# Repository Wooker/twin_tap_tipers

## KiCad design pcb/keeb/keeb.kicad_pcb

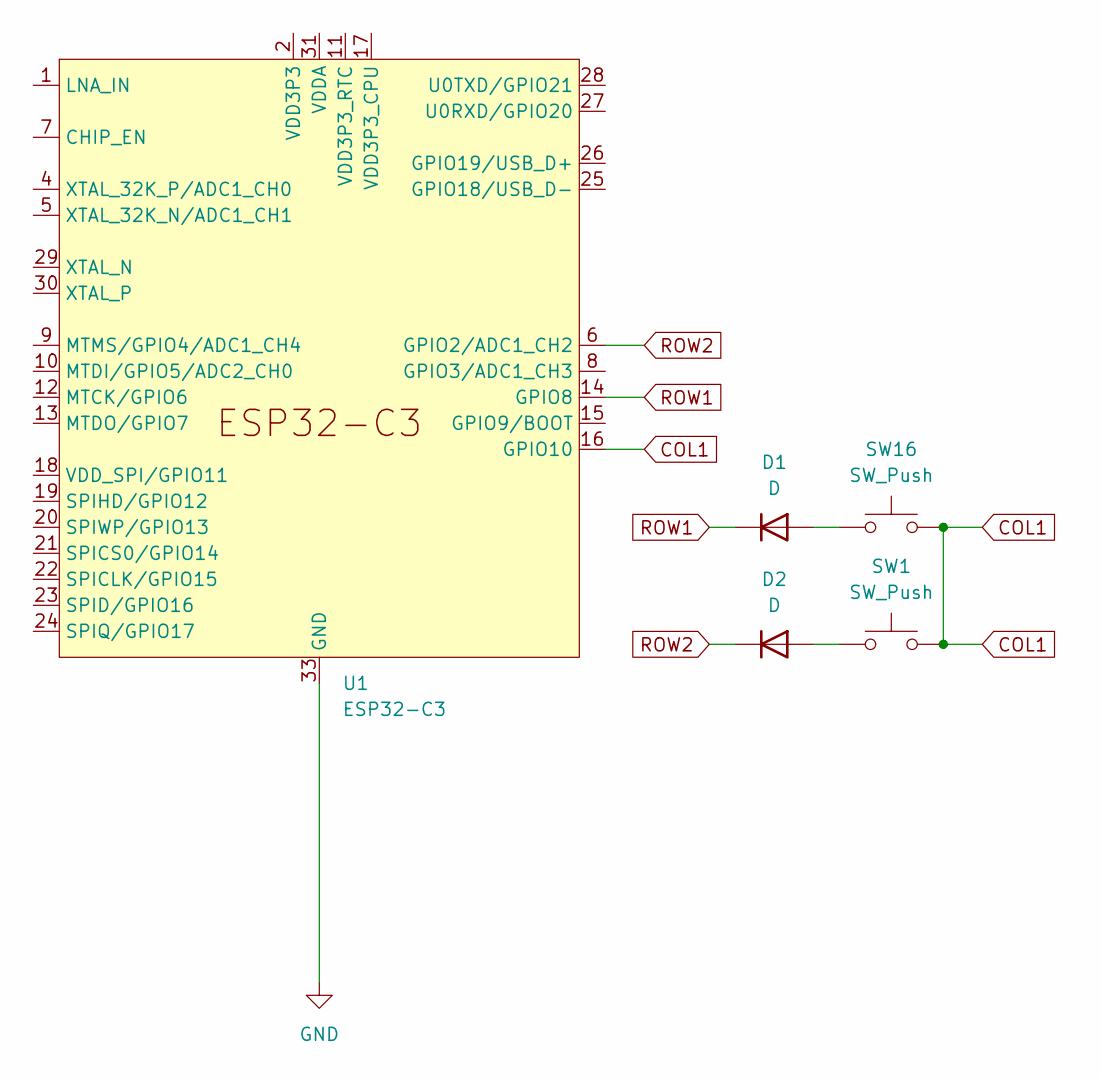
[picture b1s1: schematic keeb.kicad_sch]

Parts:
D1, D2: D; D_SOD-323_HandSoldering
SW1, SW16: SW_Push; SKPMAPE010
U1: ESP32-C3; QFN-32-1EP_5x5mm_P0.5mm_EP3.45x3.45mm

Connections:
COL1: SW1.2, SW16.2, U1.16 (GPIO10)
GND: U1.33 (GND)
unnamed: D1.2 (A), SW16.1
unnamed: D2.2 (A), SW1.1
unnamed: U1.2 (VDD3P3), U1.3 (VDD3P3)
unnamed: U1.31 (VDDA), U1.32 (VDDA)
ROW1: D1.1 (K), U1.14 (GPIO8)
ROW2: D2.1 (K), U1.6 (GPIO2/ADC1_CH2)

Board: 2 copper layers, 5 parts (0 on the bottom side), 7 nets, no tracks yet.

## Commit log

2024-03-11 Add kicad project
